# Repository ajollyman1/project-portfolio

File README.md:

# Project Portfolio

Things I've built — software (self-hosted homelab + agent tooling, incl. a Jarvis-style local AI assistant) and hardware (e-kart / e-bike / battery).

## Software, AI & self-hosting

- **[homelab](homelab/README.md)** — Linux server: local LLMs/speech, Docker Compose, Caddy, netbird, KVM, Jellyfin/*arr media stack.
- **[phone-mcp](phone-mcp/README.md)** — LLM agent drives an Android phone over ADB (MCP). No shell, kill switch, loopback-only. Includes phone-ui PWA front-end. Ongoing.
- **[voiceapi](voiceapi/README.md)** — OpenAI-compatible STT+TTS API, all local models.
- **[calendar-mcp](calendar-mcp/README.md)** — CalDAV calendar as MCP tool with write-verification.

## Hardware

- **[homemade-spot-welder](homemade-spot-welder/README.md)** — spot welder from car battery + MOSFETs. Unreliable but worked.
- **[gokart-battery-pack](gokart-battery-pack/README.md)** — 72V 20S10P pack from recycled 18650 cells (~$250 vs $600–1000).
- **[go-kart](go-kart/README.md)** — converted 3kW electric go-kart.
- **[first-ebike](first-ebike/README.md)** — 36V/500W mid-drive e-bike conversion.
- **[line-following-robot-competition](lfr/README.md)** — ENMT221 line-following robot; team 2nd; report, PCB and video.

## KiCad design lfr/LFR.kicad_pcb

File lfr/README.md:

# Line-Following Robot Competition

A line-following robot (LFR) built for **ENMT221 Mechatronics Design 1** at the University of Canterbury (Semester 2, 2026). The course runs a robot design project where every student designs a section of a line-follower individually, the team combines the best concepts into one PCB and mechanical design, and then the robots race against each other.

**Our team placed second.**

The project covered PCB design, mechanical build, programming the line-sensing → motor control loop, testing and refinement, and the race.

## Photos

## Files

- [`LFR.kicad_pcb`](LFR.kicad_pcb) — the microcontroller PCB, laid out in KiCad 10 (2-layer, 1.6 mm)
- [`report.pdf`](report.pdf) — full project report write-up (design, code, performance, reflection)
- [`media/lfr-robot.mp4`](media/lfr-robot.mp4) — a video of the robot

<video src="media/lfr-robot.mp4" controls muted width="100%"></video>

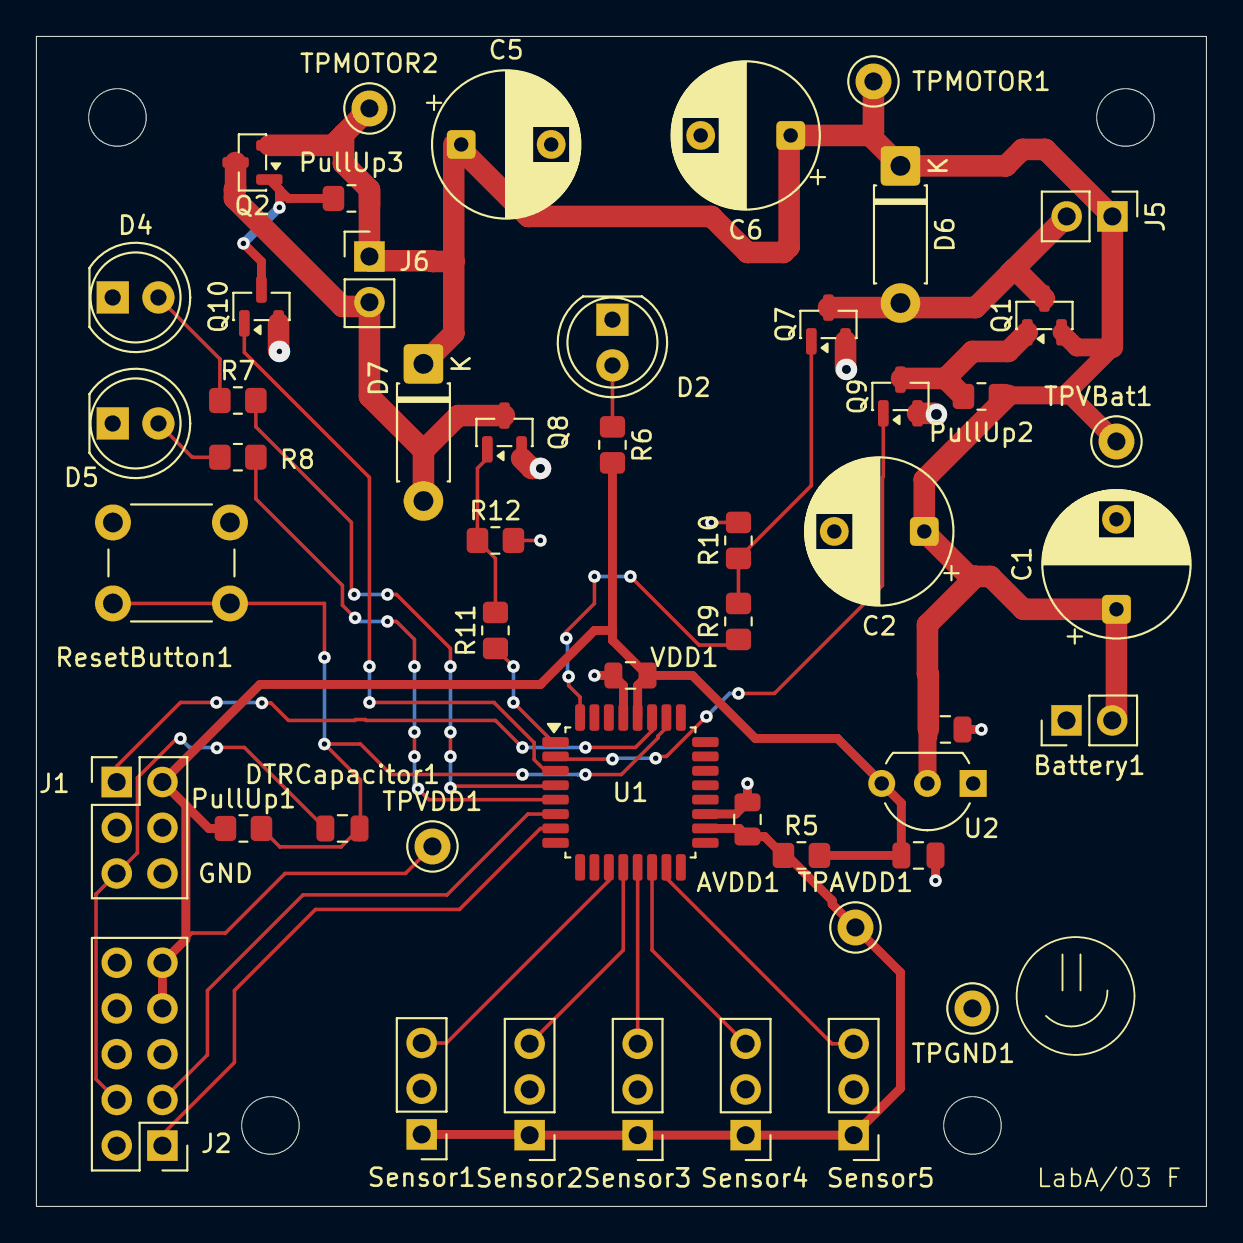
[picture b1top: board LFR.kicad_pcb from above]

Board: 2 copper layers, 65.0 x 65.0 mm, 54 parts (0 on the bottom side), 29 nets.

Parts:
AVDD1: 100n; C_0805_2012Metric
Battery1: Conn_01x02_Pin; PinHeader_1x02_P2.54mm_Vertical
C1, C2, C5, C6: 100u; CP_Radial_D8.0mm_P5.00mm
D2, D4, D5: LED; LED_D5.0mm_FlatTop
D6, D7: D_Schottky; D_DO-41_SOD81_P7.62mm_Horizontal
DTRCapacitor1: 22n; C_0805_2012Metric
DecouplingCapacitor3, DecouplingCapacitor4: 1u; C_0805_2012Metric
H1, H2, H3, H4: MountingHole; MountingHole_3.2mm_M3_ISO7380
J1: Conn_02x03_Odd_Even; PinHeader_2x03_P2.54mm_Vertical
J2: Conn_02x05_Odd_Even; PinHeader_2x05_P2.54mm_Vertical
J5, J6: Conn_01x02_Pin; PinHeader_1x02_P2.54mm_Vertical
PullUp1, PullUp2, PullUp3: 10k; R_0805_2012Metric_Pad1.20x1.40mm_HandSolder
Q1, Q2: Q_PMOS_GSD; SOT-23
Q7, Q8, Q9, Q10: BSR56; SOT-23
R5: 0; R_0805_2012Metric_Pad1.20x1.40mm_HandSolder
R6, R7, R8: 1.2k; R_0805_2012Metric_Pad1.20x1.40mm_HandSolder
R9, R11: 100; R_0805_2012Metric_Pad1.20x1.40mm_HandSolder
R10, R12: 10k; R_0805_2012Metric_Pad1.20x1.40mm_HandSolder
ResetButton1: SW_SPST; SW_PUSH_6mm_H4.3mm
Sensor1, Sensor2, Sensor3, Sensor4, Sensor5: Conn_01x03_Pin; PinHeader_1x03_P2.54mm_Vertical
TPAVDD1: TestPoint; TestPoint_Keystone_5000-5004_Miniature
TPGND1: TestPoint; TestPoint_Keystone_5000-5004_Miniature
TPMOTOR1, TPMOTOR2: TestPoint; TestPoint_Keystone_5000-5004_Miniature
TPVBat1: TestPoint; TestPoint_Keystone_5000-5004_Miniature
TPVDD1: TestPoint; TestPoint_Keystone_5000-5004_Miniature
U1: ATmega4808-A; TQFP-32_7x7mm_P0.8mm
U2: MCP1700x-330xxTO; TO-92L_Inline_Wide
VDD1: 100n; C_0805_2012Metric

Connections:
AVDD: AVDD1.1, R5.1, Sensor1.1, Sensor2.1, Sensor3.1, Sensor4.1, Sensor5.1, TPAVDD1.1 (1_1), U1.18 (AVDD)
Brake1: Q9.1 (G), U1.2 (PA4)
Brake2: Q10.1 (G), U1.3 (PA5)
ConfigLED: R7.2, U1.4 (PA6)
ConfigLED2: R8.2, U1.5 (PA7)
DTR: DTRCapacitor1.1, J1.5, J2.4
GND: AVDD1.2, Battery1.1, C1.2, C2.2, C5.2, C6.2, D2.1 (K), D4.1 (K), D5.1 (K), DecouplingCapacitor3.2, DecouplingCapacitor4.1, J1.6, J2.5, J2.6, Q7.2 (S), Q8.2 (S), Q9.2 (S), Q10.2 (S), R10.2, R12.2, ResetButton1.2 (B), Sensor1.2, Sensor2.2, Sensor3.2, Sensor4.2, Sensor5.2, TPGND1.1 (1_1), U1.19 (GND), U1.29 (GND), U2.1 (GND), VDD1.1
MOTOR1: R9.1, U1.32 (PA2)
MOTOR2: R11.1, U1.1 (PA3)
unnamed: D2.2 (A), R6.1
unnamed: D4.2 (A), R7.1
unnamed: D5.2 (A), R8.1
unnamed: D6.2 (A), J5.2, Q1.3 (D), Q7.3 (D)
unnamed: D7.2 (A), J6.2, Q2.3 (D), Q8.3 (D)
unnamed: PullUp2.2, Q1.1 (G), Q9.3 (D)
unnamed: Q7.1 (G), R9.2, R10.1
unnamed: Q8.1 (G), R11.2, R12.1
unnamed: PullUp3.2, Q2.1 (G), Q10.3 (D)
Rx: J2.1, U1.7 (PC1)
Sensor1: Sensor1.3, U1.11 (PD1)
Sensor2: Sensor2.3, U1.12 (PD2)
Sensor3: Sensor3.3, U1.13 (PD3)
Sensor4: Sensor4.3, U1.14 (PD4)
Sensor5: Sensor5.3, U1.15 (PD5)
Tx: J2.3, U1.6 (PC0)
UPDI: J1.1, U1.27 (UPDI)
VBattery: Battery1.2, C1.1, C2.1, C5.1, C6.1, D6.1 (K), D7.1 (K), DecouplingCapacitor4.2, J5.1, J6.1, PullUp2.1, PullUp3.1, Q1.2 (S), Q2.2 (S), TPMOTOR1.1 (1_1), TPMOTOR2.1 (1_1), TPVBat1.1 (1_1), U2.2 (VI)
VDD: DecouplingCapacitor3.1, J1.2, J2.7, J2.9, PullUp1.1, R5.2, R6.2, TPVDD1.1 (1_1), U1.28 (VDD), U2.3 (VO), VDD1.2
VReset: DTRCapacitor1.2, PullUp1.2, ResetButton1.1 (A), U1.26 (PF6/~RESET)
